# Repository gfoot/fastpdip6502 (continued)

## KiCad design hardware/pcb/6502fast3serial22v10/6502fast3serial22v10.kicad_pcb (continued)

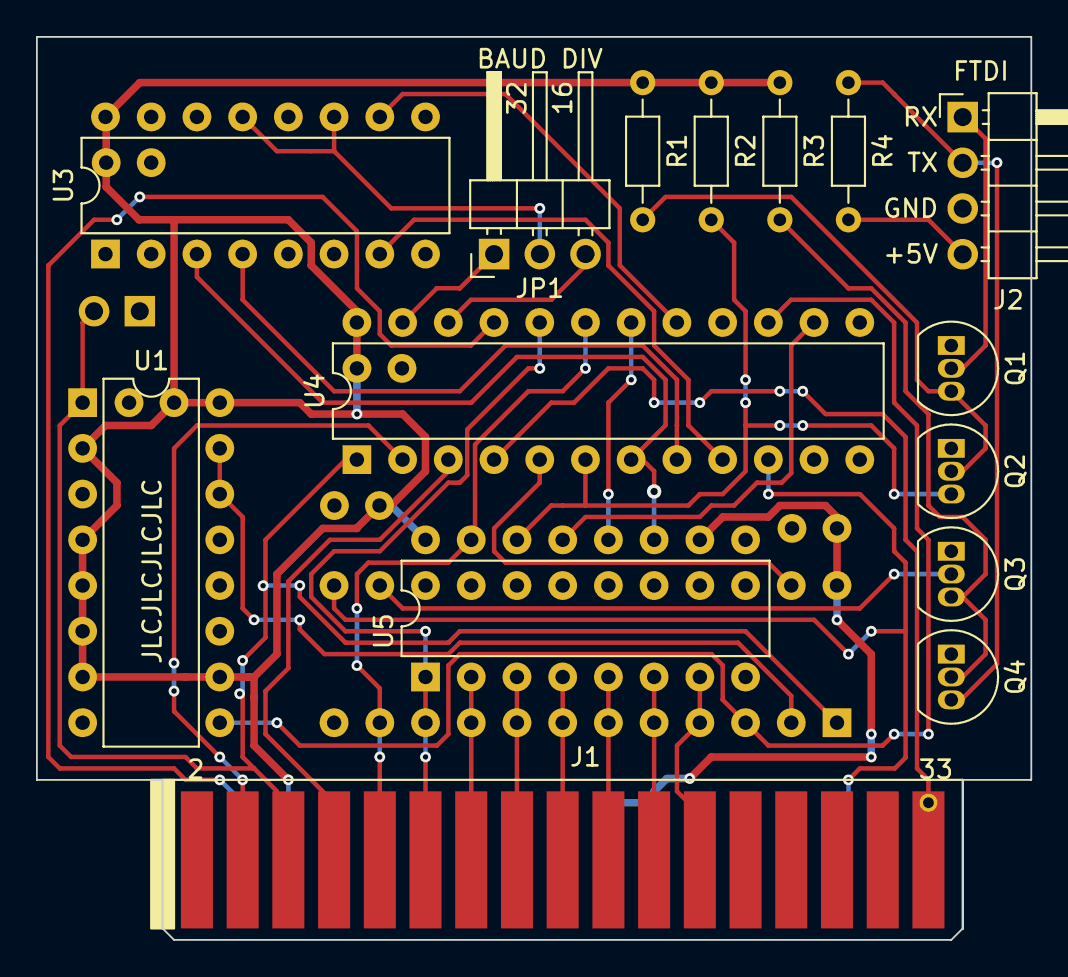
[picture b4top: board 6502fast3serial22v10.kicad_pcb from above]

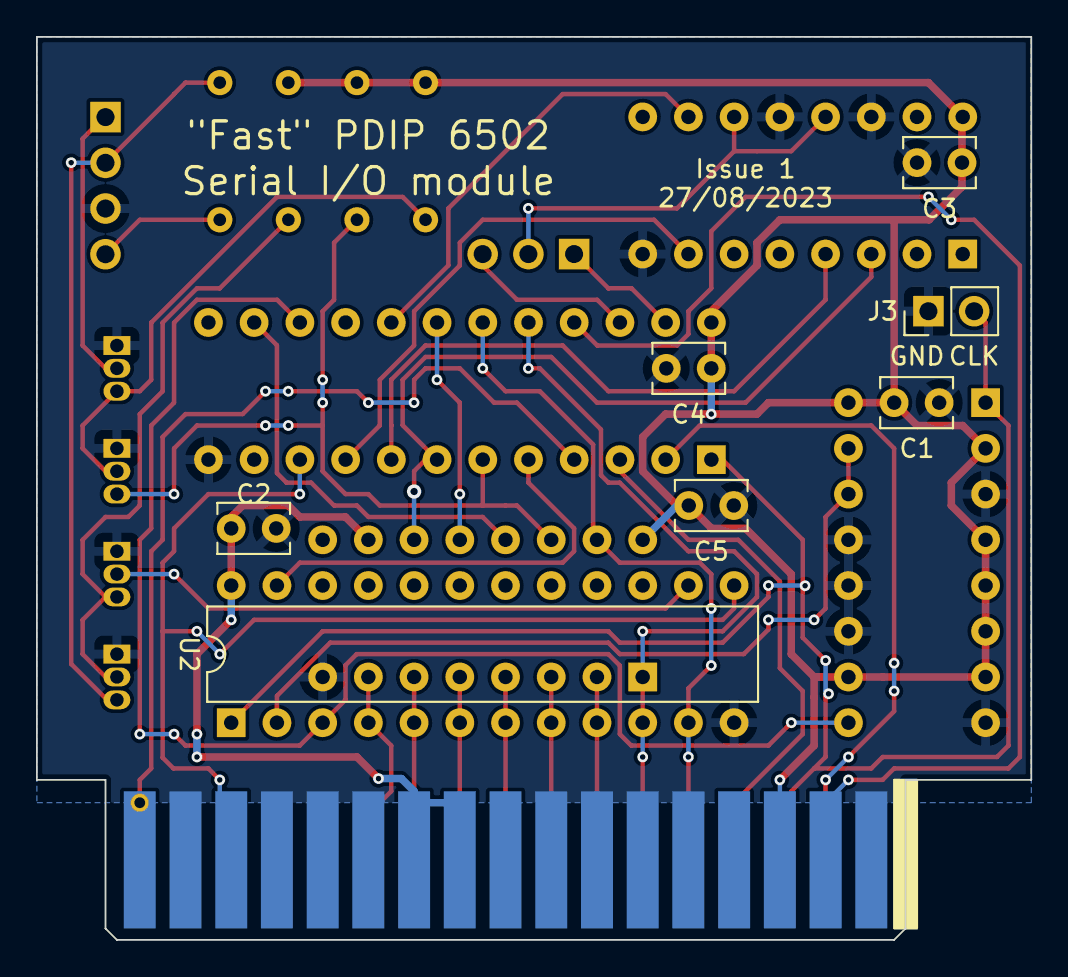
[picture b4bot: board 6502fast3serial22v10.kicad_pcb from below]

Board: 2 copper layers, 55.2 x 50.2 mm, 22 parts (7 on the bottom side), 35 nets.

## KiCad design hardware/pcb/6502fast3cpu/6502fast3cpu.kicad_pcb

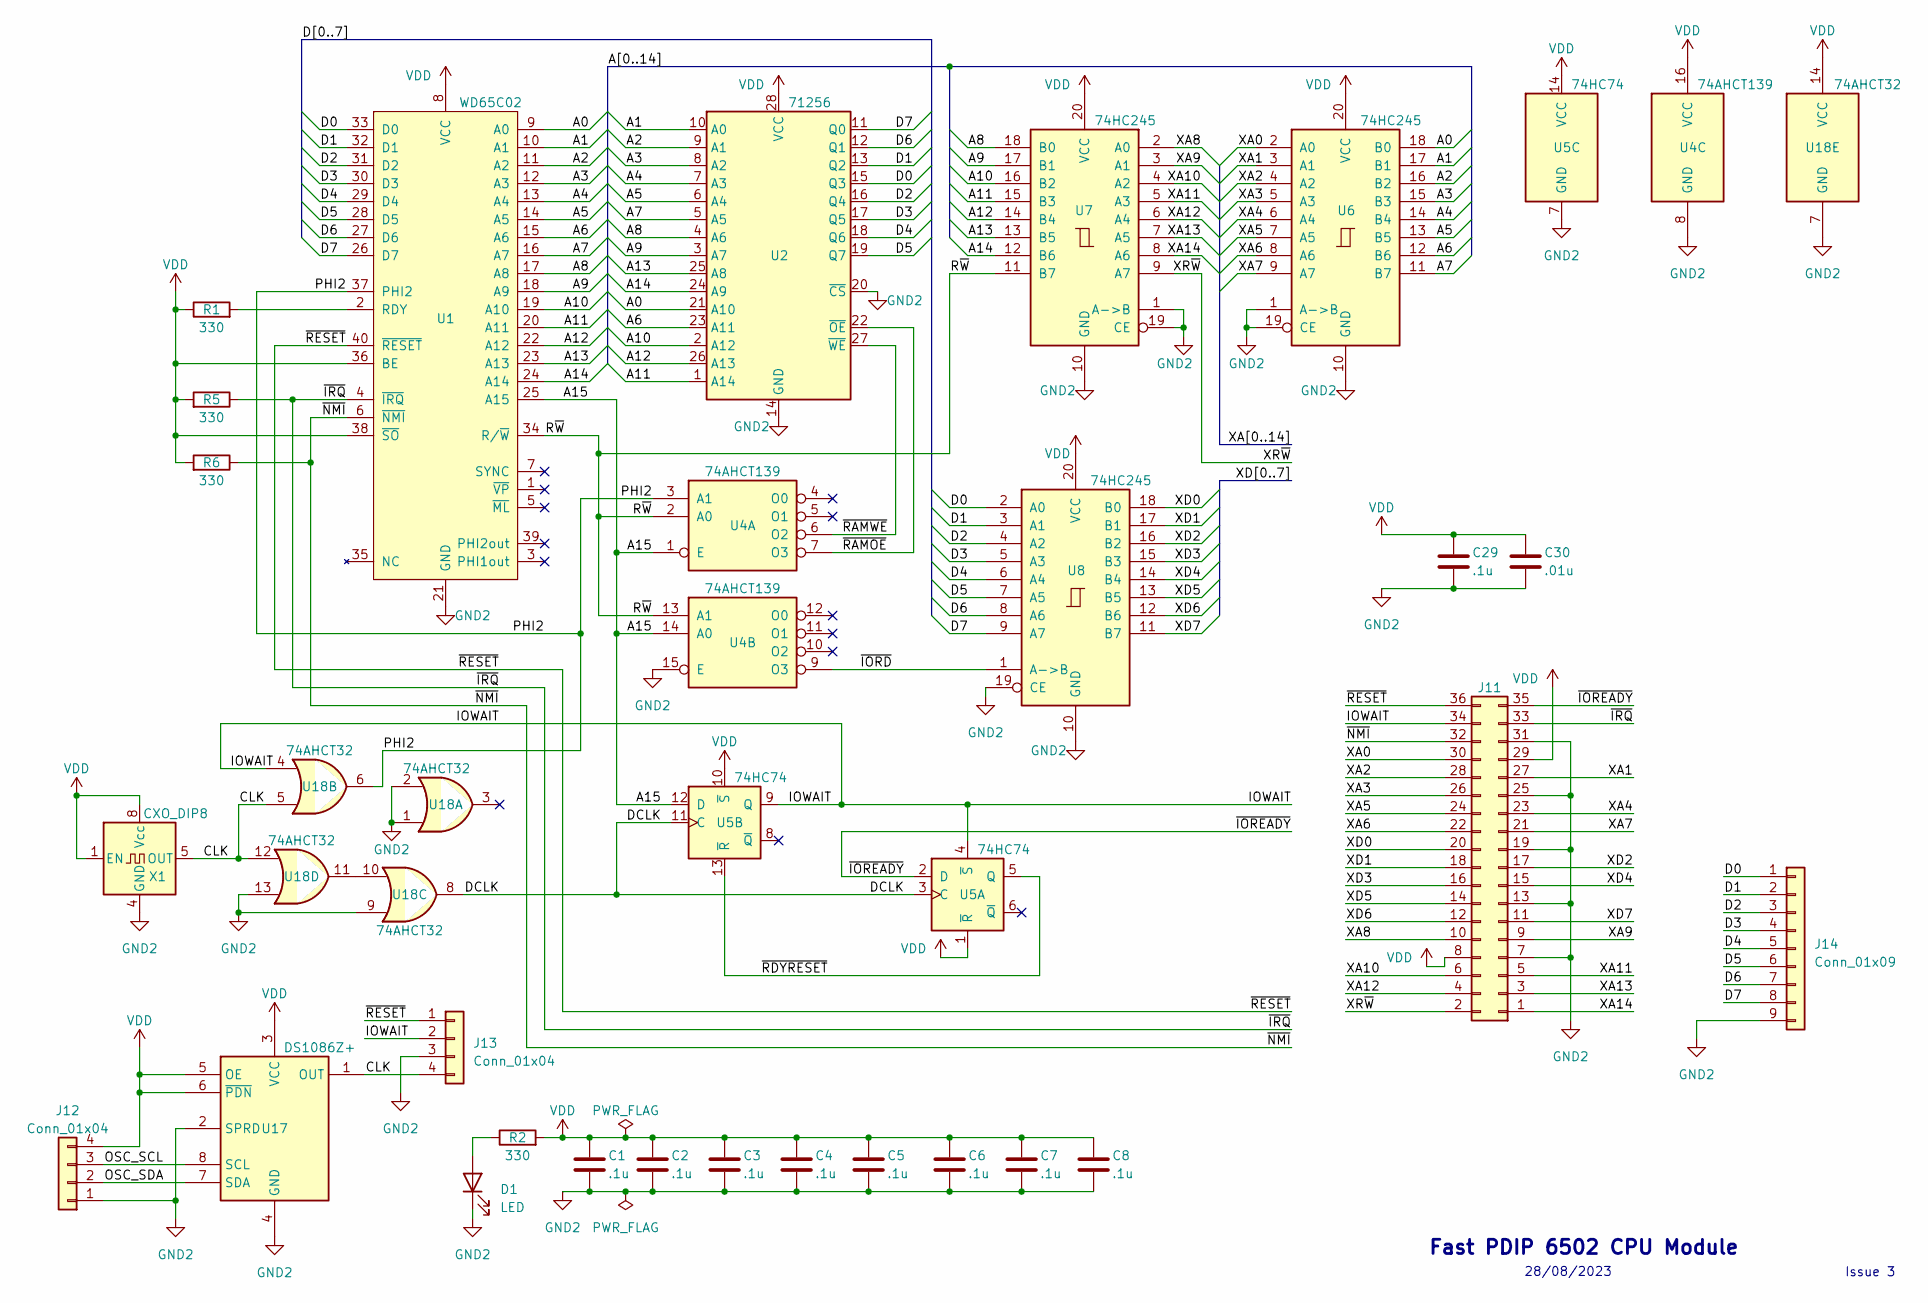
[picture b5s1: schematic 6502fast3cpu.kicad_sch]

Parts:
C1, C2, C3, C4, C5, C6, C7, C8: .1u; C_Disc_D3.0mm_W1.6mm_P2.50mm
C29: .1u; C_0603_1608Metric
C30: .01u; C_0603_1608Metric
D1: LED; LED_D5.0mm_Horizontal_O1.27mm_Z3.0mm
J11: Conn_02x18_Odd_Even; PCB_Edge_36pin
J12: Conn_01x04; PinHeader_1x04_P2.54mm_Vertical
J13: Conn_01x04; PinHeader_1x04_P2.54mm_Horizontal
J14: Conn_01x09; PinHeader_1x09_P2.54mm_Vertical
R1, R2, R5, R6: 330; R_Axial_DIN0204_L3.6mm_D1.6mm_P7.62mm_Horizontal
U1: WD65C02; DIP-40_W15.24mm_Socket
U2: 71256; DIP-28_W7.62mm
U4: 74AHCT139; DIP-16_W7.62mm
U5: 74HC74; DIP-14_W7.62mm
U6, U7, U8: 74HC245; DIP-20_W7.62mm
U17: DS1086Z+; SOIC127P600X175-8N; Mouser Part Number 700-DS1086Z
U18: 74AHCT32; DIP-14_W7.62mm
X1: CXO_DIP8; DIP-8_W7.62mm_Socket

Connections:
/A0: U1.9 (A0), U2.21 (A10), U6.18 (B0)
/A1: U1.10 (A1), U2.10 (A0), U6.17 (B1)
/A2: U1.11 (A2), U2.9 (A1), U6.16 (B2)
/A3: U1.12 (A3), U2.8 (A2), U6.15 (B3)
/A4: U1.13 (A4), U2.7 (A3), U6.14 (B4)
/A5: U1.14 (A5), U2.6 (A4), U6.13 (B5)
/A6: U1.15 (A6), U2.23 (A11), U6.12 (B6)
/A7: U1.16 (A7), U2.5 (A5), U6.11 (B7)
/A8: U1.17 (A8), U2.4 (A6), U7.18 (B0)
/A9: U1.18 (A9), U2.3 (A7), U7.17 (B1)
/A10: U1.19 (A10), U2.2 (A12), U7.16 (B2)
/A11: U1.20 (A11), U2.1 (A14), U7.15 (B3)
/A12: U1.22 (A12), U2.26 (A13), U7.14 (B4)
/A13: U1.23 (A13), U2.25 (A8), U7.13 (B5)
/A14: U1.24 (A14), U2.24 (A9), U7.12 (B6)
/A15: U1.25 (A15), U4.1 (E), U4.14 (A0), U5.12 (D)
/CLK: J13.4, U17.1 (OUT), U18.5, U18.12, X1.5 (OUT)
/D0: J14.1, U1.33 (D0), U2.15 (Q3), U8.2 (A0)
/D1: J14.2, U1.32 (D1), U2.13 (Q2), U8.3 (A1)
/D2: J14.3, U1.31 (D2), U2.16 (Q4), U8.4 (A2)
/D3: J14.4, U1.30 (D3), U2.17 (Q5), U8.5 (A3)
/D4: J14.5, U1.29 (D4), U2.18 (Q6), U8.6 (A4)
/D5: J14.6, U1.28 (D5), U2.19 (Q7), U8.7 (A5)
/D6: J14.7, U1.27 (D6), U2.12 (Q1), U8.8 (A6)
/D7: J14.8, U1.26 (D7), U2.11 (Q0), U8.9 (A7)
/DCLK: U5.3 (C), U5.11 (C), U18.8
/IOWAIT: J11.34, J13.2, U5.4 (~S), U5.9 (Q), U18.4
/OSC_SCL: J12.3, U17.8 (SCL)
/OSC_SDA: J12.2, U17.7 (SDA)
/PHI2: U1.37 (PHI2), U4.3 (A1), U18.6
/R~W: U1.34 (R/~W), U4.2 (A0), U4.13 (A1), U7.11 (B7)
/XA0: J11.30, U6.2 (A0)
/XA1: J11.27, U6.3 (A1)
/XA2: J11.28, U6.4 (A2)
/XA3: J11.26, U6.5 (A3)
/XA4: J11.23, U6.6 (A4)
/XA5: J11.24, U6.7 (A5)
/XA6: J11.22, U6.8 (A6)
/XA7: J11.21, U6.9 (A7)
/XA8: J11.10, U7.2 (A0)
/XA9: J11.9, U7.3 (A1)
/XA10: J11.6, U7.4 (A2)
/XA11: J11.5, U7.5 (A3)
/XA12: J11.4, U7.6 (A4)
/XA13: J11.3, U7.7 (A5)
/XA14: J11.1, U7.8 (A6)
/XD0: J11.20, U8.18 (B0)
/XD1: J11.18, U8.17 (B1)
/XD2: J11.17, U8.16 (B2)
/XD3: J11.16, U8.15 (B3)
/XD4: J11.15, U8.14 (B4)
/XD5: J11.14, U8.13 (B5)
/XD6: J11.12, U8.12 (B6)
/XD7: J11.11, U8.11 (B7)
/XR~W: J11.2, U7.9 (A7)
/~IORD: U4.9 (O3), U8.1 (A->B)
/~IOREADY: J11.35, U5.2 (D)
/~IRQ: J11.33, R5.1, U1.4 (~IRQ)
/~NMI: J11.32, R6.1, U1.6 (~NMI)
/~RAMOE: U2.22 (~OE), U4.7 (O3)
/~RAMWE: U2.27 (~WE), U4.6 (O2)
/~RDYRESET: U5.5 (Q), U5.13 (~R)
/~RESET: J11.36, J13.1, U1.40 (~RESET)
GND2: C1.2, C2.2, C3.2, C4.2, C5.2, C6.2, C7.2, C8.2, C29.2, C30.2, D1.1 (K), J11.7, J11.13, J11.19, J11.25, J11.31, J12.1, J13.3, J14.9, U1.21 (GND), U2.14 (GND), U2.20 (~CS), U4.8 (GND), U4.15 (E), U5.7 (GND), U6.1 (A->B), U6.10 (GND), U6.19 (CE), U7.1 (A->B), U7.10 (GND), U7.19 (CE), U8.10 (GND), U8.19 (CE), U17.2 (SPRD), U17.4 (GND), U18.1, U18.2, U18.7 (GND), U18.9, U18.13, X1.4 (GND)
unnamed: D1.2 (A), R2.1
unnamed: R1.2, U1.2 (RDY)
unnamed: U18.10, U18.11
VDD: C1.1, C2.1, C3.1, C4.1, C5.1, C6.1, C7.1, C8.1, C29.1, C30.1, J11.8, J11.29, J12.4, R1.1, R2.2, R5.2, R6.2, U1.8 (VCC), U1.36 (BE), U1.38 (~SO), U2.28 (VCC), U4.16 (VCC), U5.1 (~R), U5.10 (~S), U5.14 (VCC), U6.20 (VCC), U7.20 (VCC), U8.20 (VCC), U17.3 (VCC), U17.5 (OE), U17.6 (~PDN), U18.14 (VCC), X1.1 (EN), X1.8 (Vcc)

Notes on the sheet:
Issue 3
Fast PDIP 6502 CPU Module
28/08/2023

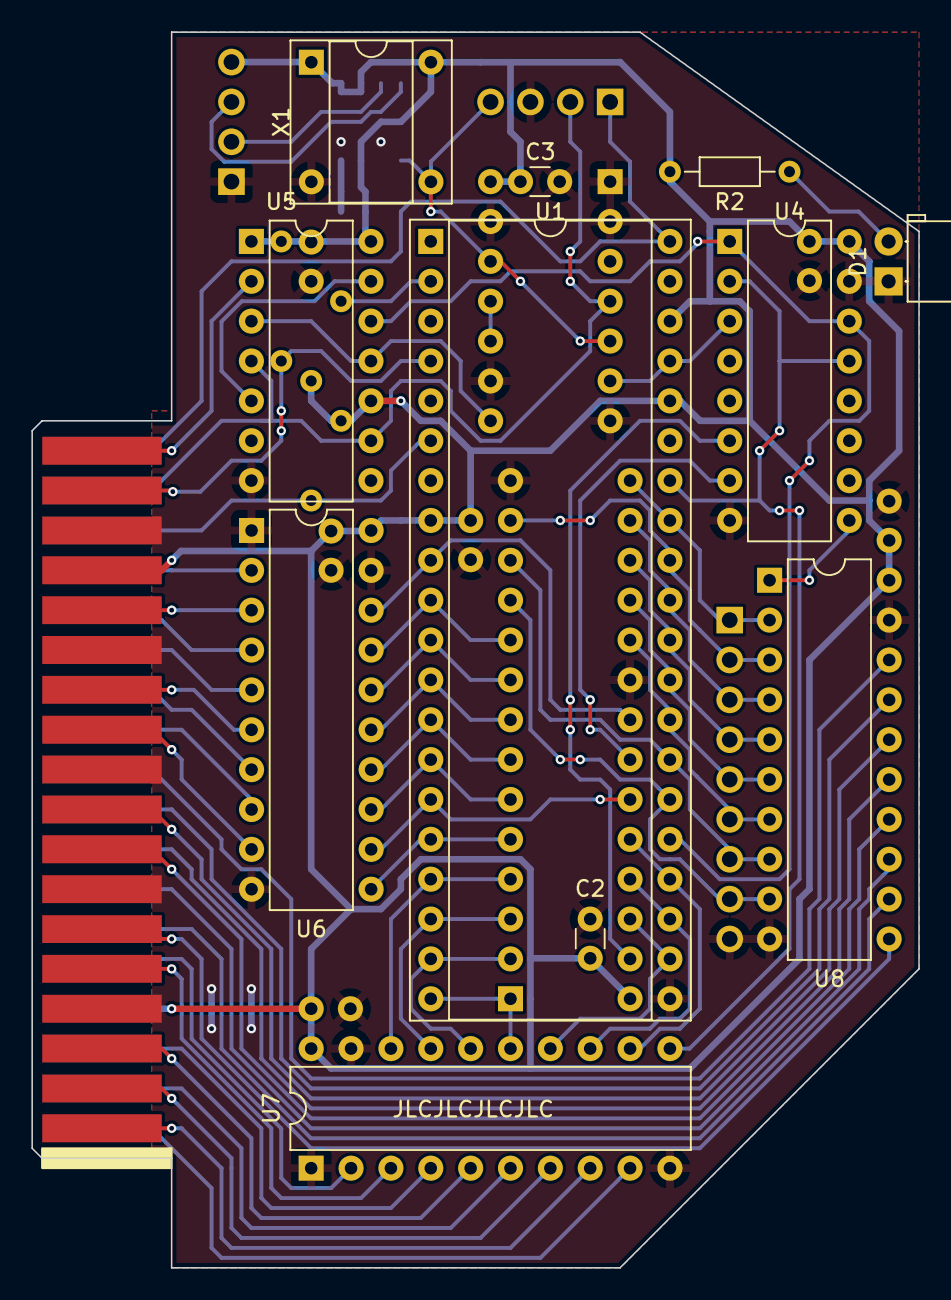
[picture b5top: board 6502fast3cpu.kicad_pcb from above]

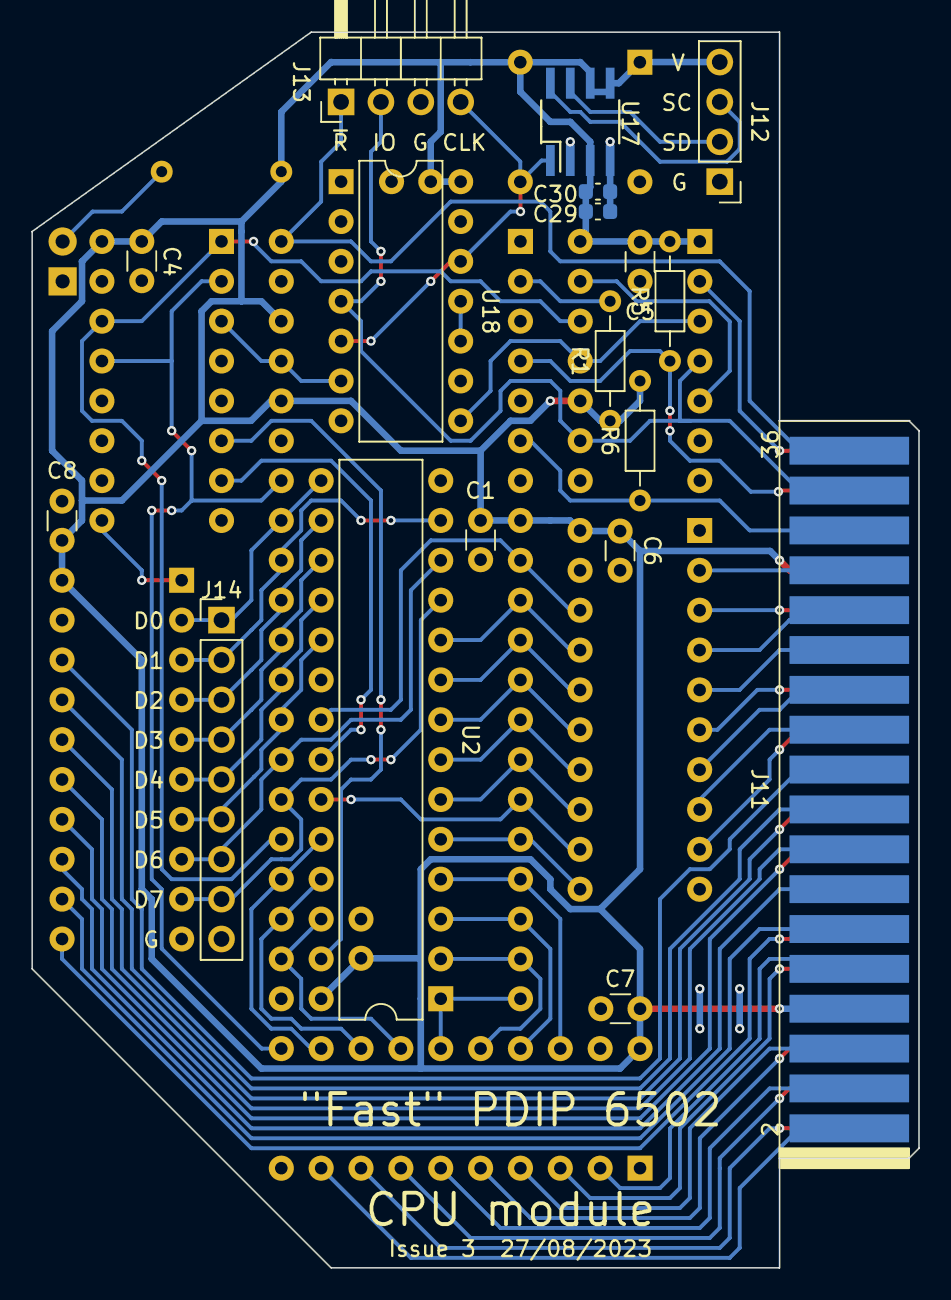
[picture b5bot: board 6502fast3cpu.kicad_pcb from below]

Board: 2 copper layers, 56.5 x 78.7 mm, 29 parts (18 on the bottom side), 68 nets.

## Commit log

2023-10-17 Snapshot of source code etc for Fast PDIP 6502 project
2023-10-17 Software source code and Hardware design files for Fast PDIP 6502 Computer
